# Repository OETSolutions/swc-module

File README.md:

# SWC — Steering Wheel Controls Adapter

A programmable interface between a vehicle's factory steering-wheel buttons and
an aftermarket Android head unit, so the buttons can be re-mapped, combined, or
given press behaviours the factory wiring never had.

**Status:** design complete and routed; 0 DRC errors, 0 unconnected, 0
schematic/PCB parity errors. **Not yet ordered.**

|  |  |
| :--: | :--: |
| **Top** — ESP32-S3 module, four left-edge screw terminals, USB-C | **Bottom** — connector pinouts silkscreened on the back |

| Item | Value |
| --- | --- |
| **Board** | 54.0 × 102.0 mm, 4-layer, 1.6 mm, rounded corners r ≈ 2.83 mm |
| **EDA** | KiCad 10 (`SWC.kicad_pcb` / `.kicad_sch` / `.kicad_pro`) |
| **Assembly** | JLCPCB, Economic PCBA, 5-off |
| **Parts** | 34 unique LCSC part types, JLCPCB-assembled |
| **MCU** | DOIT ESPS3-32-N4 (ESP32-S3-WROOM-1 clone), native USB-CDC + USB-JTAG |

## Why this exists

A steering-wheel button is not a digital switch. It is a resistor dropped across
a single analog **KEY** line; the head unit pulls that line up and identifies the
pressed button from the voltage it reads. There are usually two such lines —
this board calls them **SWC1** and **SWC2** — with the buttons split between
them.

That arrangement is cheap and robust, and also completely fixed: the resistor
values, and therefore the head unit's behaviour, live in the factory button pod.
An aftermarket head unit wants a specific resistance it was taught, or one the
user can program. This adapter supplies it by reading the ladder on one side and
*servoing* the head unit's KEY line on the other, so the mapping becomes
software. It can additionally send commands to the head unit over USB when a
button is pressed, for actions the head unit's own steering-wheel input cannot
express.

## Architecture at a glance

Two identical channels. The factory ladder is read by the ESP32-S3's ADC; the
head unit's KEY line is driven by a closed-loop servo, so the output tracks what
the board actually senses rather than what it assumes.

```text
  SWC1  J2.3 ─R1 10k─┬─ /SWC1_ADC ─────────► U3 ADC1
  SWC2  J2.2 ─R2 10k─┴─ /SWC2_ADC ─────────► U3 ADC1
        (R15/R16 10k pull-ups to +3V3 · D4/D5 BAT54S clamp · C3/C4 100nF)

  AUX1  J5.4 ─R23 1k─┬─ /AUX1_F ───────────► U3 ADC
  AUX2  J5.3 ─R24 1k─┤   /AUX2_F
  AUX3  J5.2 ─R25 1k─┴─ /AUX3_F
        (R17/R18/R19 10k pull-ups to +3V3 · D8/D9/D10 BAT54S · C15–C17 100nF)

  U3 ESP32-S3 ══ I2C, 3.3 V, R5/R6 10k pull-ups ══ U4 MCP4728  (VDD = +3V3,
       │                                              VREF = VDD, 0–3.3 V FS)
       │                                              ┌ A ─ signal, ch 1
       │                                              ├ B ─ gain mode, ch 1
       │                                              ├ C ─ signal, ch 2
       │                                              └ D ─ gain mode, ch 2
       │
       └─ per channel:  U4.VOUTx ─R46 100k─► U6x− ─(C24 100nF fb)─► U6x out
                                          U6x+ ◄─ R58 82k ─ V_buf
                                              ◄─ R61 100k ─ V_ADJ (VOUTB/D)
                        U6x out ─R52 1k─► Q4 gate ─► Q4 drain = KEY line
                        KEY ─R36 1M─► U6y buffer ─┬─► R54 10k / R50 10k ─► /SENSEx ─► U3 ADC
                                                   └─► R58 (feedback above)

  12 V ─ J1 ─ F1 PPTC ─► /+12V_SW ─► D1 SMBJ18A ─► U1 XL1509-5.0 ─► L1 47µH ─┐
                                                  (D7 SS34 freewheel)         │
  USB VBUS ─ J4 ─ F2 PPTC ─► /VBUS_FUSED ─► D3 SS34 ─┐                        │
                                                     ├─► +5V ─► U2 AMS1117 ─► +3V3
                              /+5V_BUCK ─► D2 SS34 ──┘
  NTC RT1 on /TEMP_ADC · buzzer BZ1 via Q3 · LEDs D6 / D12 · VBUS detect /VBUS_VALID
```

The three ideas that make it work:

- **The ladder is read, not re-created.** 10 kΩ series (1 kΩ on the AUX inputs),
  a BAT54S clamp to +3V3/GND, a filter, and a pull-up — so a bare
  switch-to-ground button works as well as a resistor ladder.
- **The output is a servo, not a buffer.** `V_KEY = (1 + R58/R61)·V_DAC −
  (R58/R61)·V_ADJ`, so the gain is a resistor ratio and the offset is a second
  DAC channel. That gives runtime range switching between 3 V and 5 V head
  units, and it is why the ESP32 needs no DAC of its own (the S3 has none).
- **Idle is inherently high-impedance.** The sink FET only pulls down; a command
  above the head unit's own idle voltage turns it off and the line floats back up
  through a 1 MΩ sense resistor.

Full description, including the analog detail, the power path, the USB front end,
and the reasoning behind each component choice: **[DESIGN.md](DESIGN.md)**.

## Repository guide

| Document | Contents |
| --- | --- |
| **[MANUAL.md](MANUAL.md)** | How to install and use the adapter — wiring, learning buttons, bindings, the app, firmware updates, troubleshooting |
| **[DESIGN.md](DESIGN.md)** | Requirements, block diagram, theory of operation, design rules, key design decisions |
| **[MANUFACTURING.md](MANUFACTURING.md)** | BOM generation, part list, assembly-cost analysis, fabrication output, ordering decisions |
| **[CHANGELOG.md](CHANGELOG.md)** | Revision history, accepted limitations, open items |
| **[AGENTS.md](AGENTS.md)** | How to work on the files — rules, MCP servers, skills, verify loop, gotchas. `CLAUDE.md` points here. |
| **[tools/README.md](tools/README.md)** | The sanctioned direct-write scripts, in detail |

The live project is `SWC.kicad_sch` / `SWC.kicad_pcb` / `SWC.kicad_pro` /
`SWC.kicad_sym` / the two library tables. `3dmodels/` and
`footprints/logo.pretty/` are required project-local assets; `tools/` holds the
sanctioned direct-write scripts; `SWC-backups/` and `SWC2-backups/` are the
restore path; `old/` is the 2022 RP2040 design, kept for reference only. The
full annotated layout, including what is git-ignored, is in
**[AGENTS.md](AGENTS.md)**.

## Toolchain and credits

This board was developed with a small set of external tools, all worth citing:

- **[KiCad 10](https://www.kicad.org/)** — the EDA suite. All file manipulation
  in this project goes through an MCP server rather than hand-editing.
- **[mcp-server-kicad](https://github.com/ProductOfAmerica/mcp-server-kicad)**
  (`uvx --from mcp-server-kicad mcp-server-kicad`) — the MCP server providing
  byte-preserving schematic, PCB, ERC/DRC and manufacturing-export tools. It is
  the reason every change here is scriptable and repeatable.
- **[pcbparts-mcp](https://github.com/Averyy/pcbparts-mcp)**
  (`https://pcbparts.dev/mcp`) — component search, JLCPCB stock and
  cross-reference, reference-board lookup, and PCB design rules. Used for the
  part-selection and stock-availability pass.
- **[KiStack](https://github.com/American-Embedded/kistack)** by American
  Embedded — a human-written set of KiCad skills (schematic, PCB, BOM, export,
  gerbers, footprint, symbol, panelize, product render) that standardised the
  workflow. Installed with `npx skills add American-Embedded/kistack`.
- **JLCPCB component skills** — `jlcpcb-component-finder` (part search by
  keyword, package, stock and price) and `jlcpcb-bom-generate-from-kicad` (KiCad
  BOM/position → JLCPCB PCBA order format), with its database refreshed from
  [jlcparts](https://yaqwsx.github.io/jlcparts/).

The per-tool notes and the working rules for this repository live in
**[AGENTS.md](AGENTS.md)**.

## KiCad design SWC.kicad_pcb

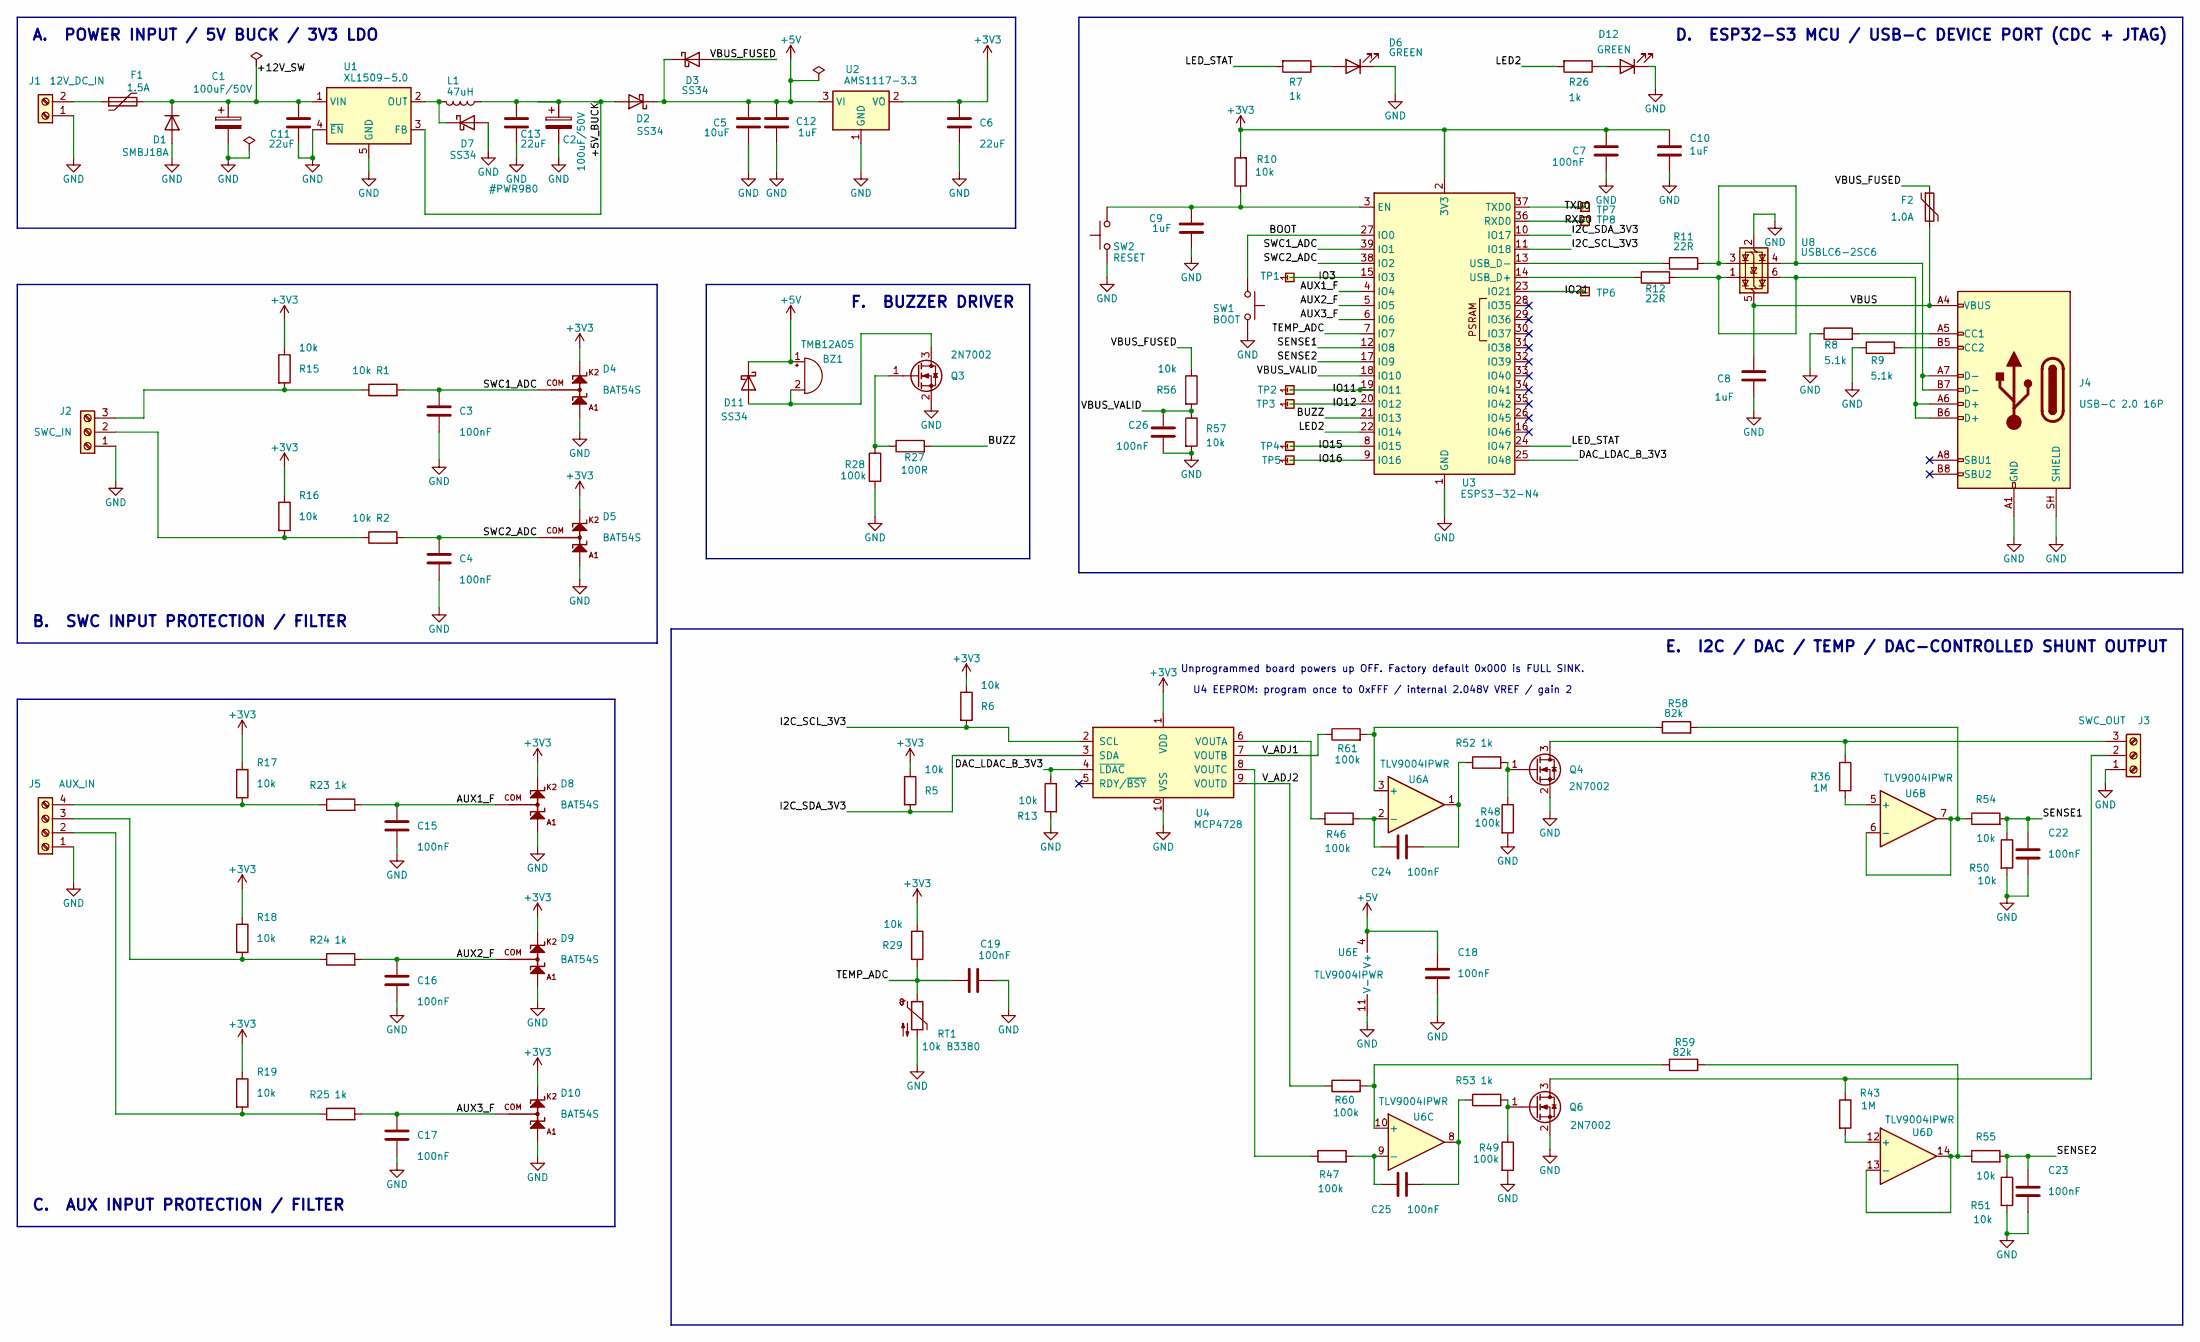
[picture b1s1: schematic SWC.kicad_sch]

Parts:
BZ1: TMB12A05; MagneticBuzzer_StarMicronics_HMB-06_HMB-12; MPN TMB12A05; LCSC C96093
C1, C2: 100uF/50V; CP_Elec_6.3x7.7; MPN JVJ50V100M6x8; LCSC C46550415
C3, C4, C7, C15, C16, C17, C18, C19, C22, C23, C24, C25, C26: 100nF; C_0805_2012Metric; MPN CC0805KRX7R9BB104; LCSC C49678
C5: 10uF; C_0805_2012Metric; MPN CL21A106KAYNNNE; LCSC C15850
C6, C11, C13: 22uF; C_0805_2012Metric; MPN CL21A226MAQNNNE; LCSC C45783
C8, C9, C10, C12: 1uF; C_0805_2012Metric; MPN CL21B105KBFNNNE; LCSC C28323
D1: SMBJ18A; D_SMB; MPN SMBJ18A; LCSC C19077573
D2, D3, D7, D11: SS34; D_SMA; MPN SS34; LCSC C8678
D4, D5, D8, D9, D10: BAT54S; SOT-23; MPN BAT54S; LCSC C7420333
D6, D12: GREEN; LED_0805_2012Metric; MPN KT-0805G; LCSC C2297
F1: 1.5A; Fuse_1812_4532Metric; MPN BSMD1812-150-33V; LCSC C883154
F2: 1.0A; Fuse_0805_2012Metric; MPN SMD0805-100-12; LCSC C46640991
J1: 12V_DC_IN; TerminalBlock_CUI_TB007-508-02_1x02_P5.08mm_Horizontal; MPN WJ500V-5.08-2P; LCSC C8465
J2: SWC_IN; TerminalBlock_CUI_TB007-508-03_1x03_P5.08mm_Horizontal; MPN WJ500V-5.08-03P; LCSC C72334
J3: SWC_OUT; TerminalBlock_CUI_TB007-508-03_1x03_P5.08mm_Horizontal; MPN WJ500V-5.08-03P; LCSC C72334
J4: USB-C 2.0 16P; USB_C_Receptacle_HRO_TYPE-C-31-M-12; MPN TYPE-C-31-M-12; LCSC C165948
J5: AUX_IN; TerminalBlock_CUI_TB007-508-04_1x04_P5.08mm_Horizontal; MPN WJ500V-5.08-04P; LCSC C42377749
L1: 47uH; L_Sunlord_MWSA0605S; MPN MWSA0605S-470MT; LCSC C408471
Q3, Q4, Q6: 2N7002; SOT-23; MPN 2N7002; LCSC C8545
R1, R2, R5, R6, R10, R13, R15, R16, R17, R18, R19, R29, R50, R51, R54, R55, R56, R57: 10k; R_0805_2012Metric; MPN 0805W8F1002T5E; LCSC C17414
R7, R23, R24, R25, R26, R52, R53: 1k; R_0805_2012Metric; MPN 0805W8F1001T5E; LCSC C17513
R8, R9: 5.1k; R_0805_2012Metric; MPN 0805W8F5101T5E; LCSC C27834
R11, R12: 22R; R_0805_2012Metric; MPN 0805W8F220JT5E; LCSC C17561
R27: 100R; R_0805_2012Metric; MPN 0805W8F1000T5E; LCSC C17408
R28, R46, R47, R48, R49, R60, R61: 100k; R_0805_2012Metric; MPN 0805W8F1003T5E; LCSC C149504
R36, R43: 1M; R_0805_2012Metric; MPN 0805W8F1004T5E; LCSC C17514
R58, R59: 82k; R_0805_2012Metric; MPN 0805W8F8202T5E; LCSC C17840
RT1: 10k B3380; R_0603_1608Metric; MPN SDNT1608X103F3380FTF; LCSC C316397
SW1: BOOT; SW_SPST_TS-1088-xR020; MPN TS-1088-AR02016; LCSC C720477
SW2: RESET; SW_SPST_TS-1088-xR020; MPN TS-1088-AR02016; LCSC C720477
TP1, TP2, TP3, TP4, TP5, TP6, TP7, TP8: TestPoint; TestPoint_THTPad_2.0x2.0mm_Drill1.0mm
U1: XL1509-5.0; SOIC-8_3.9x4.9mm_P1.27mm; MPN XL1509-5.0E1; LCSC C61063
U2: AMS1117-3.3; SOT-223-3_TabPin2; MPN AMS1117-3.3; LCSC C6186
U3: ESPS3-32-N4; ESP32-S3-WROOM-1; MPN ESPS3-32-N4; LCSC C49164655
U4: MCP4728; MSOP-10_3x3mm_P0.5mm; MPN MCP4728T-E/UN; LCSC C478093
U6: TLV9004IPWR; TSSOP-14_4.4x5mm_P0.65mm; MPN TLV9004IPWR; LCSC C2058050
U8: USBLC6-2SC6; SOT-23-6; MPN USBLC6-2SC6; LCSC C7519

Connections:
+3V3: C6.1, C7.1, C10.1, D4.2 (K2), D5.2 (K2), D8.2 (K2), D9.2 (K2), D10.2 (K2), R5.1, R6.1, R10.2, R15.1, R16.1, R17.1, R18.1, R19.1, R29.1, U2.2 (VO), U3.2 (3V3), U4.1 (VDD)
/+5V_BUCK: C2.1, C13.1, D2.2 (A), L1.1, U1.3 (FB)
/AUX1_F: C15.1, D8.3 (COM), R23.2, U3.4 (IO4)
/AUX2_F: C16.1, D9.3 (COM), R24.2, U3.5 (IO5)
/AUX3_F: C17.1, D10.3 (COM), R25.2, U3.6 (IO6)
/BOOT: SW1.1, U3.27 (IO0)
/BUZZ: R27.2, U3.21 (IO13)
/DAC_LDAC_B_3V3: R13.1, U3.25 (IO48), U4.4 (~LDAC)
/I2C_SCL_3V3: R6.2, U3.11 (IO18), U4.2 (SCL)
/I2C_SDA_3V3: R5.2, U3.10 (IO17), U4.3 (SDA)
/IO3: TP1.1 (~_1), U3.15 (IO3)
/IO11: TP2.1 (~_1), U3.19 (IO11)
/IO12: TP3.1 (~_1), U3.20 (IO12)
/IO15: TP4.1 (~_1), U3.8 (IO15)
/IO16: TP5.1 (~_1), U3.9 (IO16)
/IO21: TP6.1 (~_1), U3.23 (IO21)
/LED2: R26.2, U3.22 (IO14)
/LED_STAT: R7.2, U3.24 (IO47)
/RXD0: TP8.1 (~_1), U3.36 (RXD0)
/SENSE1: C22.1, R50.1, R54.2, U3.12 (IO8)
/SENSE2: C23.1, R51.1, R55.2, U3.17 (IO9)
/SWC1_ADC: C3.1, D4.3 (COM), R1.2, U3.39 (IO1)
/SWC2_ADC: C4.1, D5.3 (COM), R2.2, U3.38 (IO2)
/TEMP_ADC: C19.1, R29.2, RT1.1, U3.7 (IO7)
/TXD0: TP7.1 (~_1), U3.37 (TXD0)
/VBUS: C8.1, F2.2, J4.A4 (VBUS), J4.A9 (VBUS), J4.B4 (VBUS), J4.B9 (VBUS), U8.5 (VBUS)
/VBUS_FUSED: D3.2 (A), F2.1, R56.1
/VBUS_VALID: C26.1, R56.2, R57.1, U3.18 (IO10)
/V_ADJ1: R61.1, U4.7 (VOUTB)
/V_ADJ2: R60.1, U4.9 (VOUTD)
unnamed: BZ1.2 (-), D11.2 (A), Q3.3 (D)
unnamed: C24.2, R52.1, U6.1
unnamed: C25.2, R53.1, U6.8
unnamed: D6.2 (A), R7.1
unnamed: D7.1 (K), L1.2, U1.2 (OUT)
unnamed: D12.2 (A), R26.1
unnamed: F1.1, J1.2
unnamed: J2.2, R2.1, R16.2
unnamed: J2.3, R1.1, R15.2
unnamed: J3.2, Q6.3 (D), R43.1
unnamed: J3.3, Q4.3 (D), R36.1
unnamed: J4.A5 (CC1), R8.2
unnamed: J4.B5 (CC2), R9.2
unnamed: J4.A6 (D+), J4.B6 (D+), R12.2, U8.1 (I/O1), U8.6 (I/O1)
unnamed: J4.A7 (D-), J4.B7 (D-), R11.2, U8.3 (I/O2), U8.4 (I/O2)
unnamed: J5.2, R19.2, R25.1
unnamed: J5.3, R18.2, R24.1
unnamed: J5.4, R17.2, R23.1
unnamed: Q3.1 (G), R27.1, R28.1
unnamed: Q4.1 (G), R48.1, R52.2
unnamed: Q6.1 (G), R49.1, R53.2
unnamed: C9.2, R10.1, SW2.2, U3.3 (EN)
unnamed: R12.1, U3.14 (USB_D+)
unnamed: R11.1, U3.13 (USB_D-)
unnamed: R46.1, U4.6 (VOUTA)
unnamed: R47.1, U4.8 (VOUTC)
unnamed: R58.1, R61.2, U6.3 (+)
unnamed: C24.1, R46.2, U6.2 (-)
unnamed: R36.2, U6.5 (+)
unnamed: R54.1, R58.2, U6.6 (-), U6.7
unnamed: R59.1, R60.2, U6.10 (+)
unnamed: C25.1, R47.2, U6.9 (-)
unnamed: R43.2, U6.12 (+)
unnamed: R55.1, R59.2, U6.13 (-), U6.14

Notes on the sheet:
A. POWER INPUT / 5V BUCK / 3V3 LDO
F. BUZZER DRIVER
C. AUX INPUT PROTECTION / FILTER
B. SWC INPUT PROTECTION / FILTER
U4 EEPROM: program once to 0xFFF / internal 2.048V VREF / gain 2
E. I2C / DAC / TEMP / DAC-CONTROLLED SHUNT OUTPUT
D. ESP32-S3 MCU / USB-C DEVICE PORT (CDC + JTAG)
Unprogrammed board powers up OFF. Factory default 0x000 is FULL SINK.

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
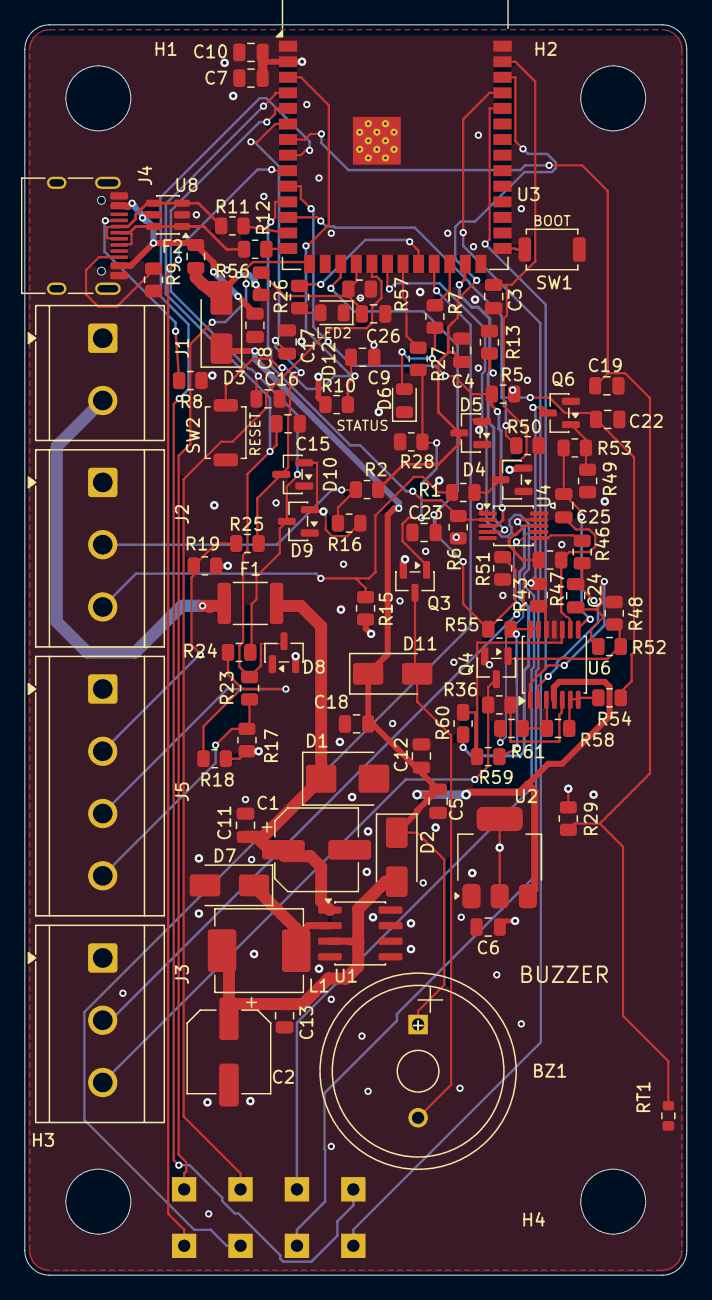
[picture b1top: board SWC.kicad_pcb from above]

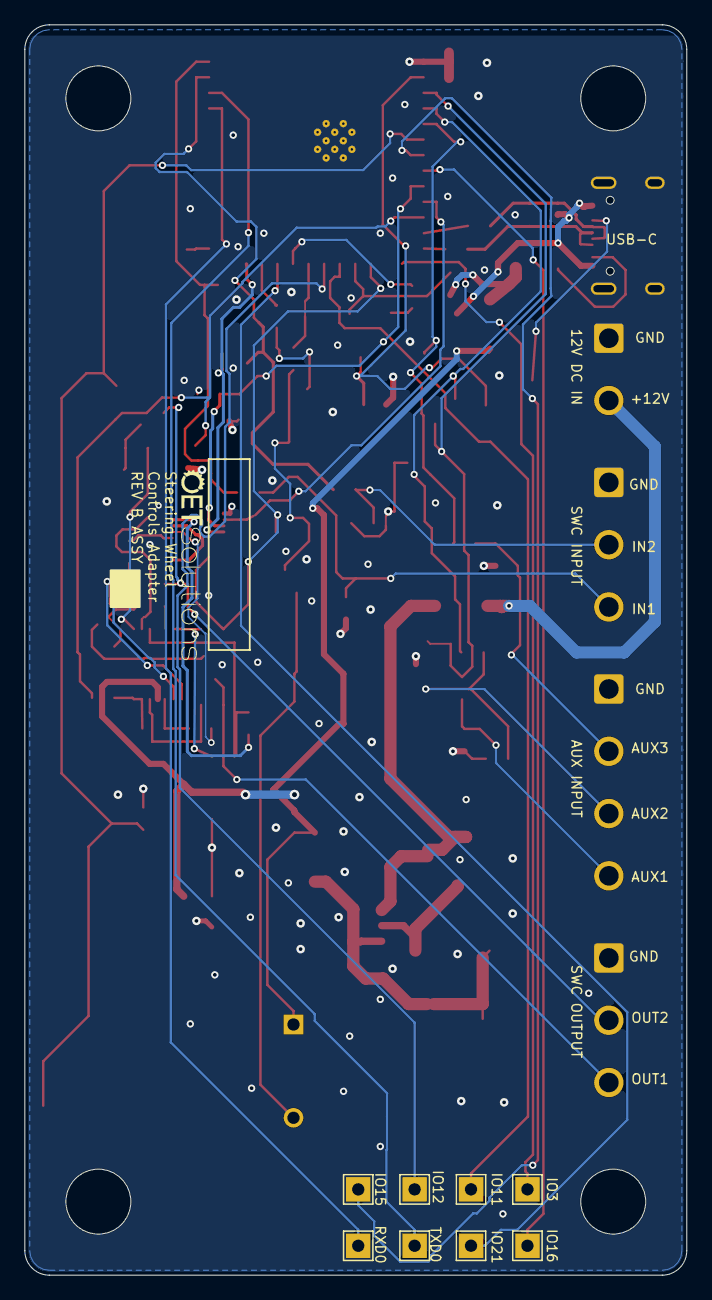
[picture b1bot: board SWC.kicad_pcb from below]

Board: 4 copper layers, 54.0 x 102.0 mm, 110 parts (9 on the bottom side), 67 nets.

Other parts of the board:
G1: LOGO
H1, H2, H3, H4: MountingHole_5.3mm_M5

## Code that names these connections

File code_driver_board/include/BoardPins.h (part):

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// Analog inputs (all ADC1 -- spec 2.2; ADC2 is unusable while WiFi is up, and
// WiFi is on for most of this tool's life)
// ---------------------------------------------------------------------------
#define PIN_SWC1_ADC      1    // /SWC1_ADC   ADC1_CH0, ladder 1, R1 10k series
#define PIN_SWC2_ADC      2    // /SWC2_ADC   ADC1_CH1, ladder 2, R2 10k series
#define PIN_TEMP_ADC      7    // /TEMP_ADC   ADC1_CH6, NTC RT1 divider
#define PIN_SENSE1        8    // /SENSE1     ADC1_CH7, KEY1 voltage / 2
#define PIN_SENSE2        9    // /SENSE2     ADC1_CH8, KEY2 voltage / 2
#define PIN_AUX1          4    // /AUX1_F     ADC1_CH3, 1k series, R17 10k pull-up
#define PIN_AUX2          5    // /AUX2_F     ADC1_CH4, 1k series, R18 10k pull-up
#define PIN_AUX3          6    // /AUX3_F     ADC1_CH5, 1k series, R19 10k pull-up

// ---------------------------------------------------------------------------
// Digital
// ---------------------------------------------------------------------------
#define PIN_VBUS_VALID   10    // D-in,  VBUS present via R56/R57 divider
#define PIN_BUZZ         13    // D-out, buzzer Q3 gate via R27 100R
#define PIN_LED2         14    // D-out, D12 via R26 1k
#define PIN_LED_STAT     47    // D-out, D6 via R7 1k
#define PIN_I2C_SDA      17    // I2C to U4 MCP4728
#define PIN_I2C_SCL      18    // I2C to U4 MCP4728
#define PIN_DAC_LDAC_B   48    // D-out, MCP4728 ~LDAC, R13 10k pulldown
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// LED polarity, and why it is a constant rather than an inline HIGH/LOW
// ---------------------------------------------------------------------------
// The netlist shows D6/D12 with cathode on the LED net and anode off it, and the
// series resistors R7/R26 return to /LED_STAT and /LED2 -- i.e. the GPIO drives
// the resistor into the ANODE and the cathode is tied to GND (net "ND" is the
// unconnected/GND-side pad here, as it is for R50, R57, RT1 and R57's divider
// returns). So the port pin HIGH lights the LED. That is also the polarity the
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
